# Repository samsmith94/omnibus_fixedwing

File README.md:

# Supplementary board for Omnibus F4 V3.

With this board, you can relocate your Omnibus Flight Controller to another model, since soldering is not required at all.

It is very convenient to use with the on-board
- GY-NEO8MV2 pin header
- 3-pin JST connector for FPV camera
- 3-pin JST connector for FPV transmitter
- 6-pin JST connector for Racerstar Shot30AESC
- 3-pin connector for WS2812B LED strip
- piezo buzzer.

Additionally there is an RFM95 LoRa modul + Atmega 328P + SMA connector for experimental LoRa-RC.

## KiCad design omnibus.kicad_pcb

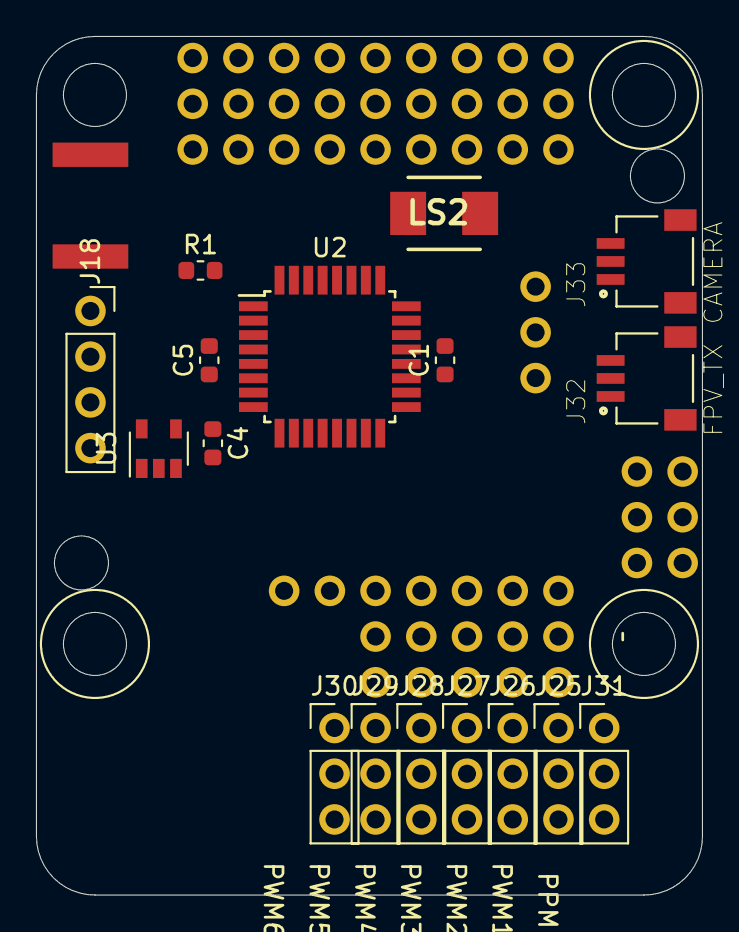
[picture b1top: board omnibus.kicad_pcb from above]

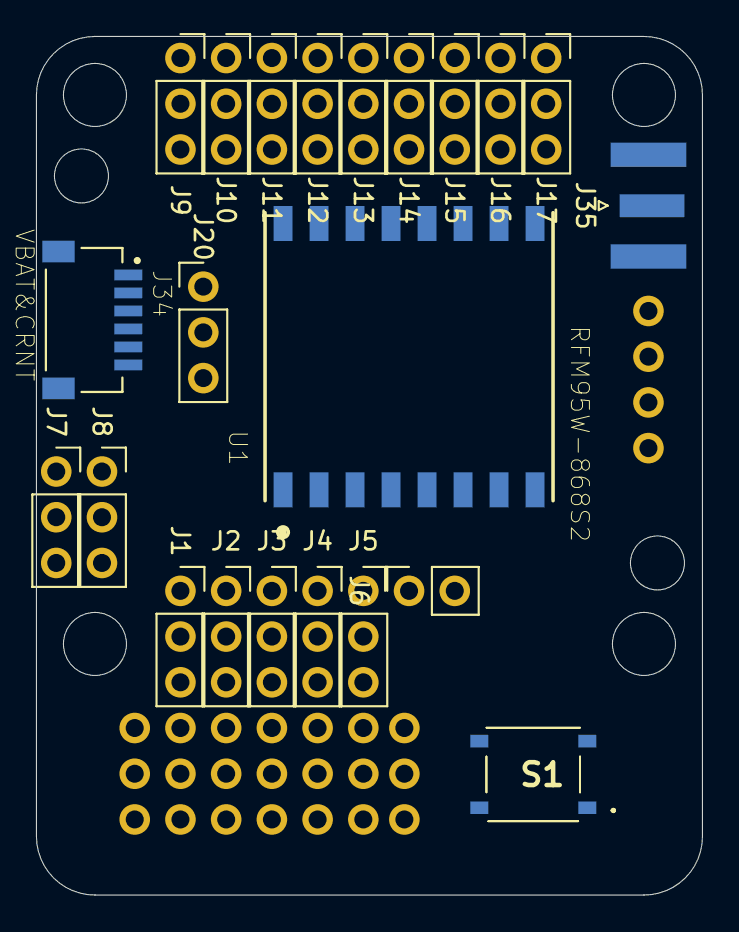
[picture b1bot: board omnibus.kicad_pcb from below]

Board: 2 copper layers, 37.0 x 47.7 mm, 39 parts (22 on the bottom side), 30 nets, no tracks yet.

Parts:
C1, C4, C5: 0,1uF; C_0603_1608Metric
J1: RC; PinSocket_1x03_P2.54mm_Vertical
J2: PWM1; PinSocket_1x03_P2.54mm_Vertical
J3: PWM2; PinSocket_1x03_P2.54mm_Vertical
J4: PWM3; PinSocket_1x03_P2.54mm_Vertical
J5: PWM4; PinSocket_1x03_P2.54mm_Vertical
J6: PWM5&6; PinSocket_1x02_P2.54mm_Vertical
J7: VIN; PinSocket_1x03_P2.54mm_Vertical
J8: VOUT; PinSocket_1x03_P2.54mm_Vertical
J9: LED; PinSocket_1x03_P2.54mm_Vertical
J10: BUZ; PinSocket_1x03_P2.54mm_Vertical
J11: VBAT; PinSocket_1x03_P2.54mm_Vertical
J12: CRNT&SCL/TX3; PinSocket_1x03_P2.54mm_Vertical
J13: RSSI&SDA/RX3; PinSocket_1x03_P2.54mm_Vertical
J14: GND; PinSocket_1x03_P2.54mm_Vertical
J15: 5V; PinSocket_1x03_P2.54mm_Vertical
J16: RAM&TX1&TX6; PinSocket_1x03_P2.54mm_Vertical
J17: RX1&RX6; PinSocket_1x03_P2.54mm_Vertical
J18: GPS; PinSocket_1x04_P2.54mm_Vertical
J20: LED_STRIP; PinHeader_1x03_P2.54mm_Vertical
J25, J26, J27, J28, J29, J30, J31: Conn_01x03_Male; PinHeader_1x03_P2.54mm_Vertical
J32: FPV_TX; JST_SM03B-SRSS-TB(LF)(SN)
J33: CAMERA; JST_SM03B-SRSS-TB(LF)(SN)
J34: VBAT&CRNT; JST_SM06B-SRSS-TB(LF)(SN)
J35: Conn_Coaxial; SMA_Samtec_SMA-J-P-H-ST-EM1_EdgeMount
LS2: CMT-4023S-SMT-TR; CMT-4023S
R1: 10k; R_0603_1608Metric
S1: PTS526_SK08_SMTR2_LFS; PTS526SKG15SMTR2LFS
U1: RFM95W-868S2; XCVR_RFM95W-868S2
U2: ATmega328P-AU; TQFP-32_7x7mm_P0.8mm
U3: MIC5205-3.3YM5; SOT-23-5

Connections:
+3V3: C4.1, C5.1, R1.1, U1.13, U2.4, U2.6, U2.18, U3.5
+5V: J1.2, J2.2, J3.2, J4.2, J5.2, J9.2, J11.3, J15.1, J15.2, J15.3, J18.1, J20.1
CRNT: J12.2, J34.1
DO: J9.3, J20.2
GND: C1.2, C4.2, C5.2, J1.3, J2.3, J3.3, J4.3, J5.3, J9.1, J10.3, J11.1, J12.1, J13.1, J14.1, J14.2, J14.3, J18.4, J20.3, J25.3, J26.3, J27.3, J28.3, J29.3, J30.3, J32.2, J33.2, J34.5, J34.6, J35.2, S1.4, U1.1, U1.8, U1.10, U2.3, U2.5, U2.21, U3.2
GNDA: J7.1, J8.1
MISO: U1.2, U2.16
MOSI: U1.3, U2.15
unnamed: C1.1, U2.20
unnamed: U3.1, U3.3
unnamed: J32.S1, J32.S2
unnamed: J33.S1, J33.S2
unnamed: J34.S1, J34.S2
unnamed: J35.1, U1.9
PPM_FROM_RC: J1.1, J31.1
PWM1: J2.1, J25.1
PWM2: J3.1, J26.1
PWM3: J4.1, J27.1
PWM4: J5.1, J28.1
PWM5: J6.1, J29.1
PWM6: J6.2, J30.1
RAM: J7.2, J8.2, J16.1
RESET: R1.2, S1.2, U1.6, U2.29
RX: J16.2, J18.2
RX1: J17.2, J18.3
SCK: U1.4, U2.17
SS: U1.5, U2.14
VBAT: J11.2, J17.1, J34.2
VIN: J7.3, J33.1
VOUT: J8.3, J32.1

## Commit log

2020-03-19 Create RAEDME
2020-03-19 Rename RAEDME to README.md
2020-03-19 add 3d model
